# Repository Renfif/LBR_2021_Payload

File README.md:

# LBR 2021 Payload
PJS and UAS code for LBR USLI 2021
##

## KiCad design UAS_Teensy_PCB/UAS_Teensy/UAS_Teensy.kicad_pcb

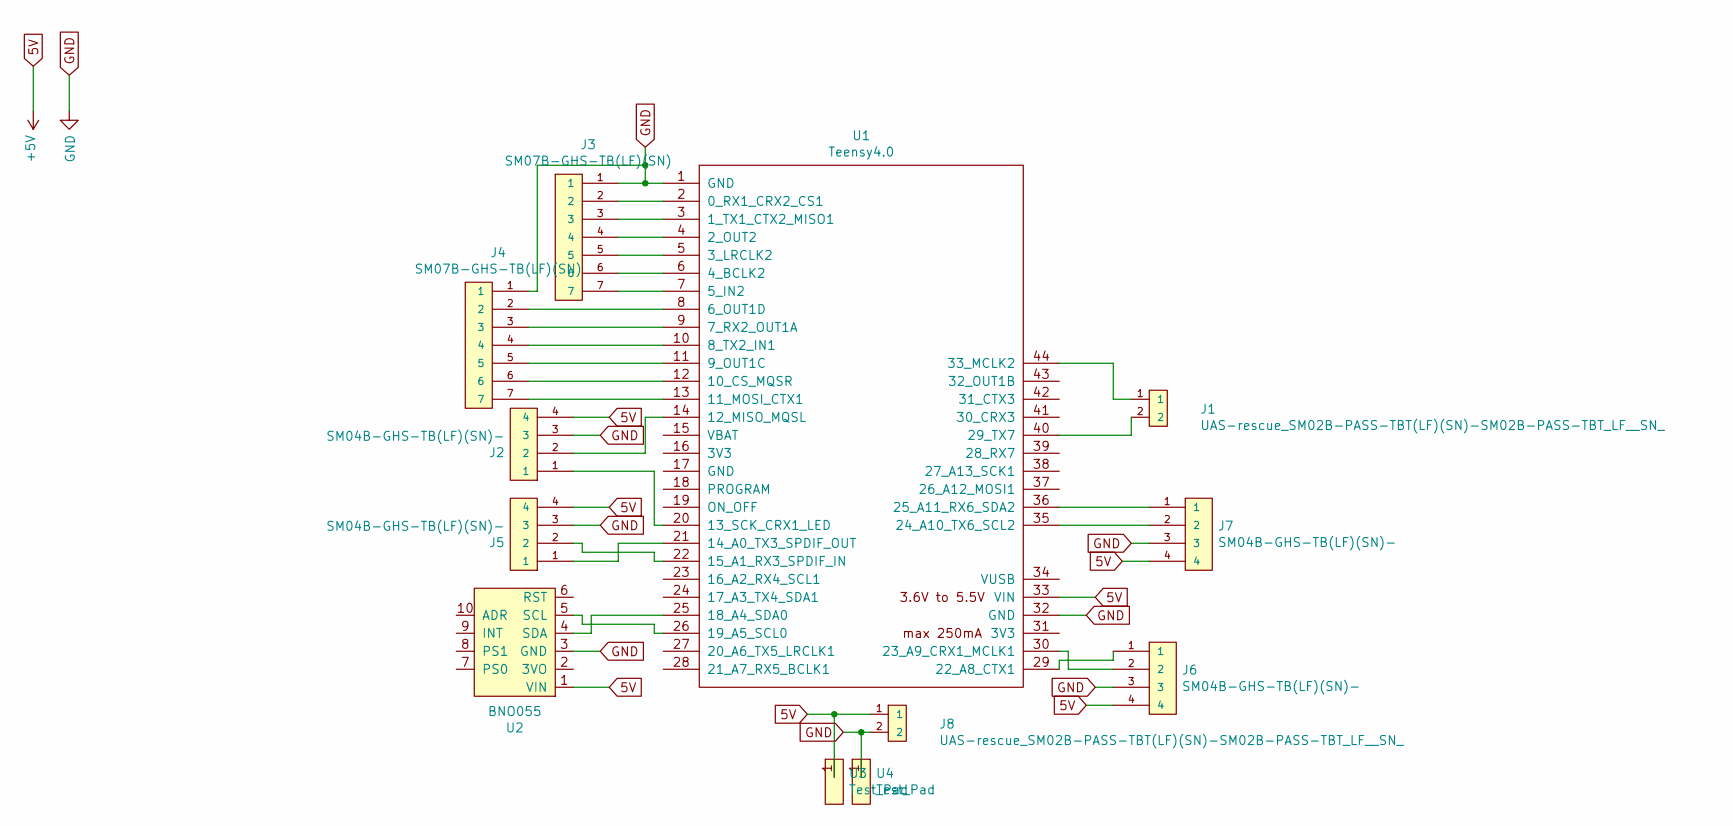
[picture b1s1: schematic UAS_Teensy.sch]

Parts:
J1, J8: UAS-rescue_SM02B-PASS-TBT(LF)(SN)-SM02B-PASS-TBT_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; SM02BGHSTBLFSN; PARTREV N/A
J2, J5, J6, J7: SM04B-GHS-TB(LF)(SN)-; JST_SM04B-GHS-TB(LF)(SN)-; PARTREV NA
J3, J4: SM07B-GHS-TB(LF)(SN); JST_SM08B-GHS-TB(LF)(SN); PARTREV NA
U1: Teensy4.0; Teensy40
U2: BNO055; BNO055_Breakout
U3, U4: Test_Pad; Individual_Solder_Pad

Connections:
5V: J2.4, J5.4, J6.4, J7.4, J8.1, U1.33 (VIN), U2.1 (VIN), U3.1
GND: J2.3, J3.1, J4.1, J5.3, J6.3, J7.3, J8.2, U1.1 (GND), U1.32 (GND), U2.3 (GND), U4.1
unnamed: J1.1, U1.44 (33_MCLK2)
unnamed: J1.2, U1.40 (29_TX7)
unnamed: J2.1, U1.20 (13_SCK_CRX1_LED)
unnamed: J2.2, U1.14 (12_MISO_MQSL)
unnamed: J3.2, U1.2 (0_RX1_CRX2_CS1)
unnamed: J3.3, U1.3 (1_TX1_CTX2_MISO1)
unnamed: J3.4, U1.4 (2_OUT2)
unnamed: J3.5, U1.5 (3_LRCLK2)
unnamed: J3.6, U1.6 (4_BCLK2)
unnamed: J3.7, U1.7 (5_IN2)
unnamed: J4.2, U1.8 (6_OUT1D)
unnamed: J4.3, U1.9 (7_RX2_OUT1A)
unnamed: J4.4, U1.10 (8_TX2_IN1)
unnamed: J4.5, U1.11 (9_OUT1C)
unnamed: J4.6, U1.12 (10_CS_MQSR)
unnamed: J4.7, U1.13 (11_MOSI_CTX1)
unnamed: J5.1, U1.21 (14_A0_TX3_SPDIF_OUT)
unnamed: J5.2, U1.22 (15_A1_RX3_SPDIF_IN)
unnamed: J6.1, U1.29 (22_A8_CTX1)
unnamed: J6.2, U1.30 (23_A9_CRX1_MCLK1)
unnamed: J7.1, U1.36 (25_A11_RX6_SDA2)
unnamed: J7.2, U1.35 (24_A10_TX6_SCL2)
unnamed: U1.25 (18_A4_SDA0), U2.4 (SDA)
unnamed: U1.26 (19_A5_SCL0), U2.5 (SCL)

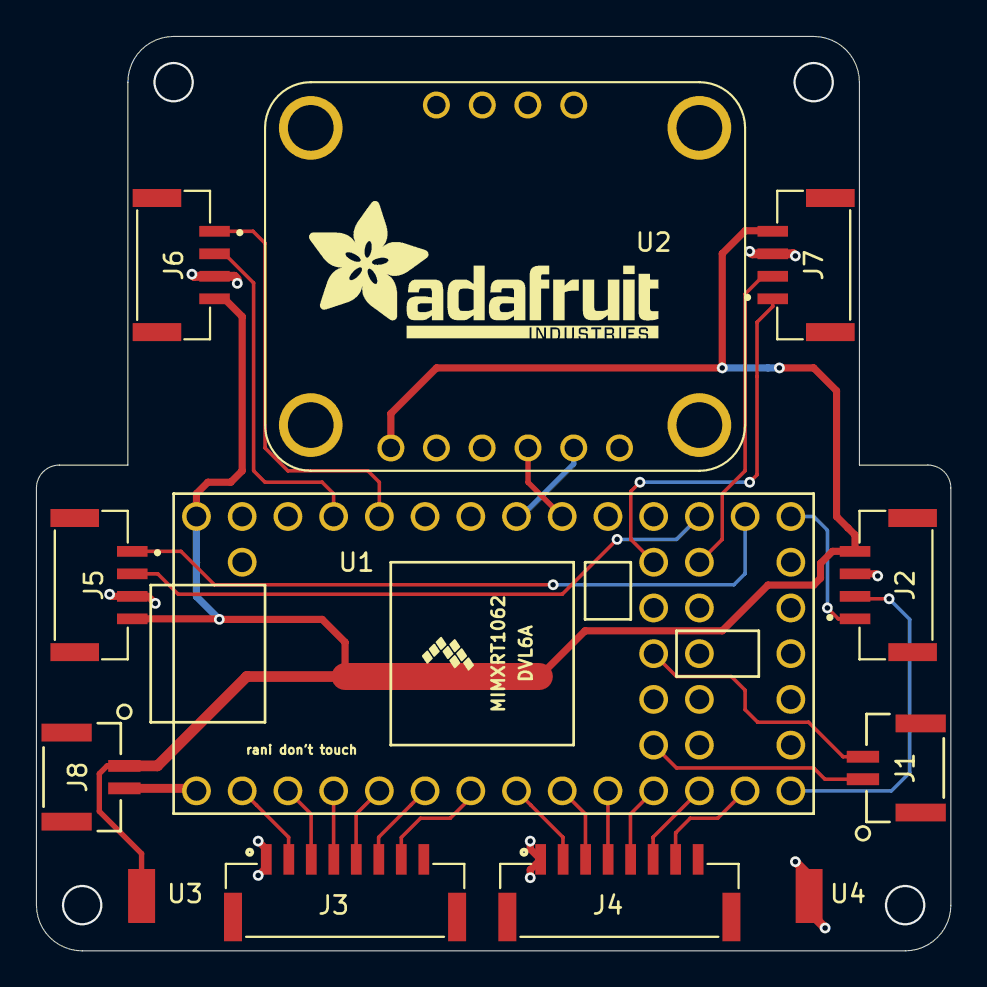
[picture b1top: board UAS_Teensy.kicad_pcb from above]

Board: 2 copper layers, 50.8 x 50.8 mm, 13 parts (0 on the bottom side), 26 nets.

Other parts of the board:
N2: V20180719; Label_version

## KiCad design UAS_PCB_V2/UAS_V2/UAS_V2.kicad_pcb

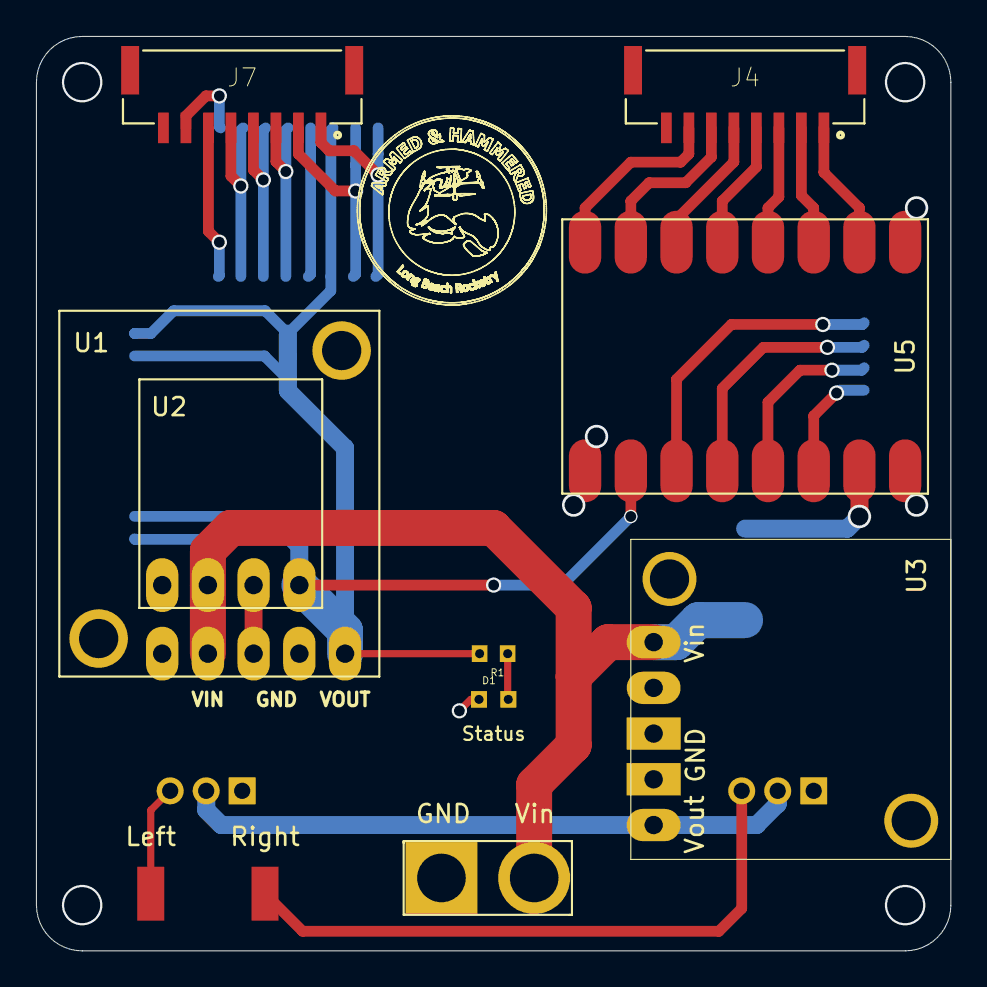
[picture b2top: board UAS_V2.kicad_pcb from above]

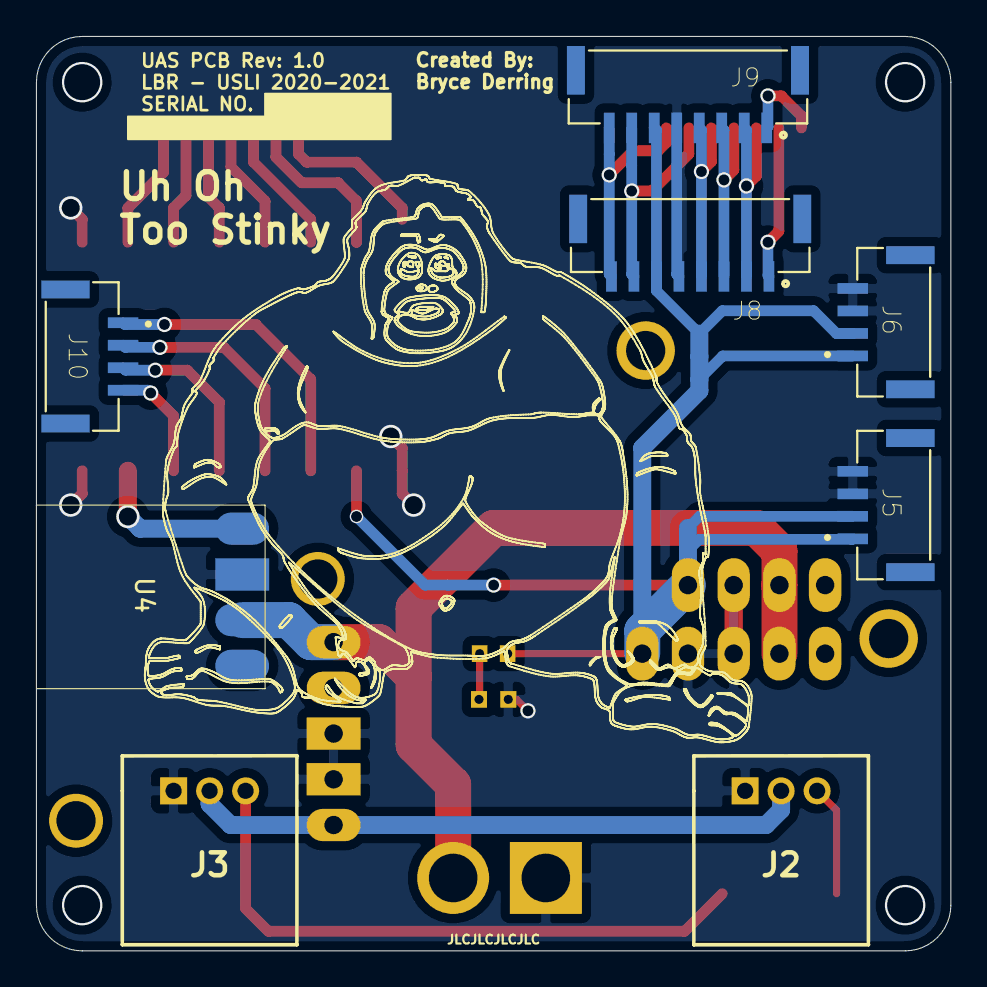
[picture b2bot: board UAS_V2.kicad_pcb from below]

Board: 2 copper layers, 50.8 x 50.8 mm, 20 parts (8 on the bottom side), 26 nets.

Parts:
D1: Device_LED; Indicator-LED
J1: UAS_PWR_IN; UAS_PCB_PWR_IN_PTOS
J2, J3: UAS_JST-3-pin-Revised-Symbol; MOLEX_SHDRRA3W50P0X200_1X3_0353630360
J4, J7: UAS_SM07B-GHS-TB(LF)(SN); JST_SM08B-GHS-TB(LF)(SN)
J5, J6, J10: UAS_SM04B-GHS-TB(LF)(SN)-; JST_SM04B-GHS-TB(LF)(SN)-
J8, J9: UAS_SM08B-GHS-TB(LF)(SN); JST_SM08B-GHS-TB(LF)(SN)
Left: UAS-rescue_Signal-Pad-UAS-cache; Individual_Solder_Pad
N2: V20180719; Label_version
R1: CR0603-JW-152ELF; RESC1608X55N
Right: UAS-rescue_Signal-Pad-UAS-cache; Individual_Solder_Pad
U1: UAS-rescue_5A-5V-Converter-UAS-cache; Pololu_5V_5A_Step_Down_Regulator
U2: UAS-rescue_500mA-5V-Converter-UAS-cache; Pololu_5V_500mA_Step_Down_Regulator
U3: 7.5V-2.5A-Step-Down(old); Pololu_7.75V_2.5A_Step_Down_Regulator(old)
U4: 12V_500mA_Step_Up; Pololu_12V_Step_Down_Regulator
U5: UAS-rescue_TB6612FNG-Dual-Motor-Driver-UAS-cache; Pololu_TB6612_Dual_Motor_Driver_Carrier_SMT

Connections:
+5V: J5.1, J5.2, J6.1, J6.2, J8.6, J9.6, R1.2, U1.5, U2.4, U5.2
+7.5V: J2.2, J3.2, U3.5
+12V: U4.4, U5.7
+24V: J1.2, U1.2, U2.2, U3.1, U4.2
GND: D1.1, J1.1, J2.1, J3.1, J5.3, J5.4, J6.3, J6.4, J8.5, J9.5, U1.3, U1.4, U2.3, U3.3, U3.4, U4.3, U5.1, U5.8, U5.16
unnamed: D1.2, R1.1
unnamed: J2.3, Left.1
unnamed: J3.3, Right.1
unnamed: J4.1, U5.15
unnamed: J4.2, U5.14
unnamed: J4.3, U5.13
unnamed: J4.4, U5.12
unnamed: J4.5, U5.11
unnamed: J4.6, U5.10
unnamed: J4.7, U5.9
unnamed: J7.1, J8.8, J9.8
unnamed: J7.2, J8.7, J9.7
unnamed: J7.3, J8.4, J9.4
unnamed: J7.4, J8.3, J9.3
unnamed: J7.5, J8.2, J9.2
unnamed: J7.6, J8.1
unnamed: J7.7, J9.1
unnamed: J10.1, U5.3
unnamed: J10.2, U5.4
unnamed: J10.3, U5.5
unnamed: J10.4, U5.6

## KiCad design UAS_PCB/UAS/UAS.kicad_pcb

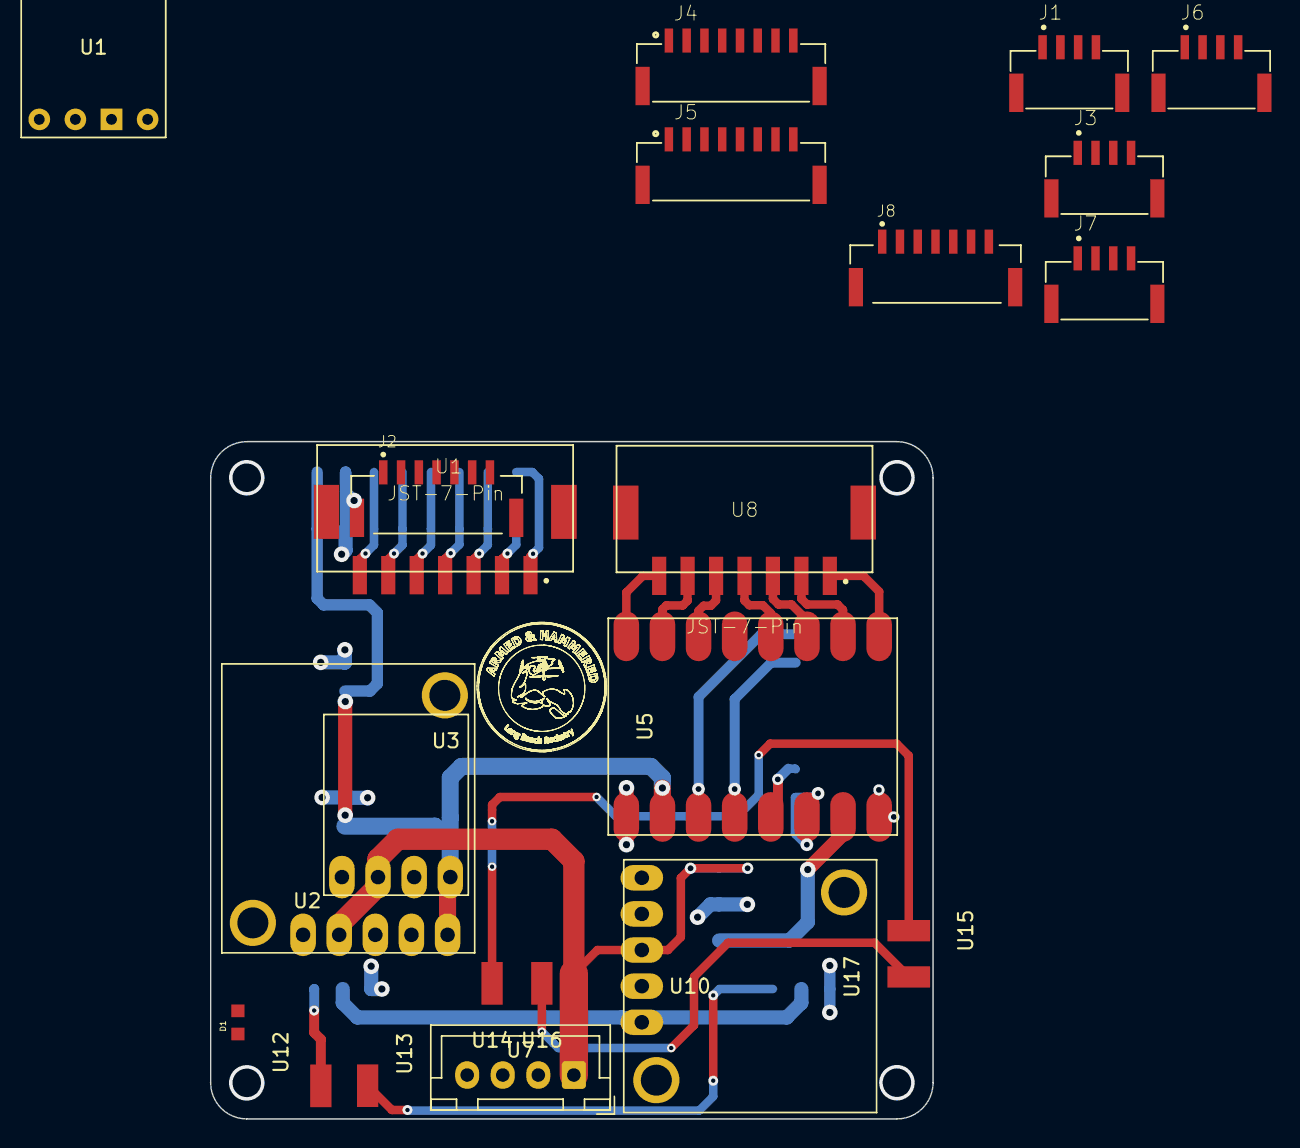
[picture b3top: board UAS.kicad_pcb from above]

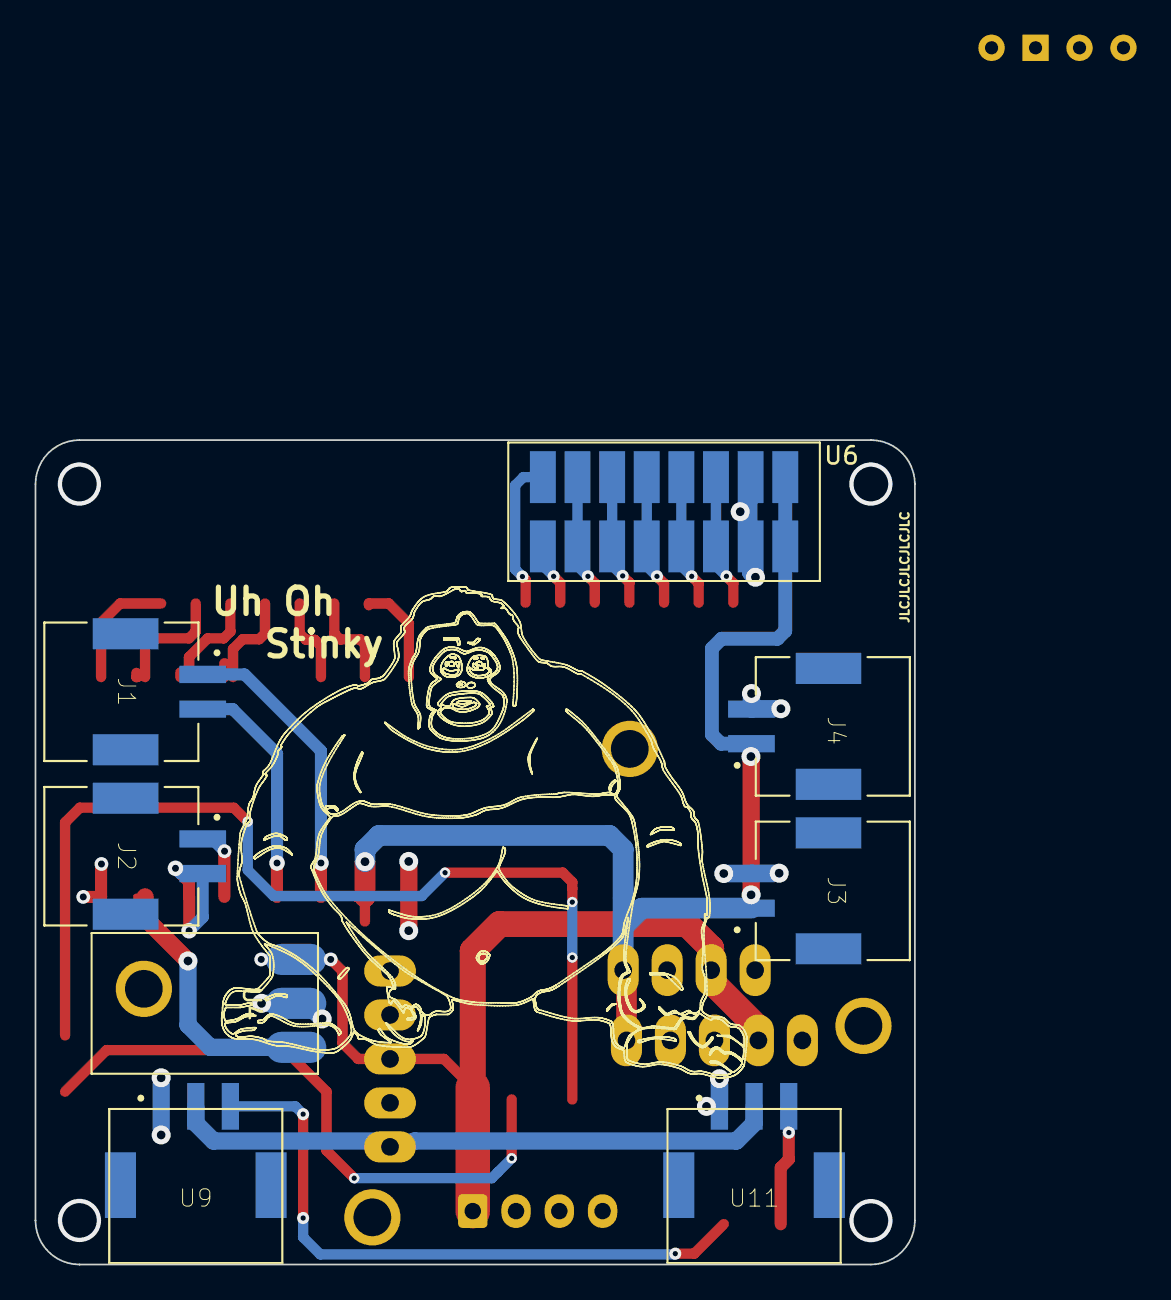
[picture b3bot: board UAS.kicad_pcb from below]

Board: 2 copper layers, 50.8 x 47.6 mm, 31 parts (8 on the bottom side), 36 nets.

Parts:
D1: LED; Indicator-LED
J1, J3, J6, J7: SM04B-GHS-TB(LF)(SN)-; JST_SM04B-GHS-TB(LF)(SN)-
J1#2, J2#2, J3#2, J4#2: SM02B-PASS-TBT; JST_SM02B-PASS-TBT(LF)(SN)
J2, J8: SM07B-GHS-TB(LF)(SN); JST_SM07B-GHS-TB(LF)(SN)
J4, J5: SM08B-GHS-TB(LF)(SN); JST_SM08B-GHS-TB(LF)(SN)
U1: 12V-500mA-StepDown
U1#2, U8: JST-7-Pin; JST_SM07B-PASS-TBT(LF)(SN)
U2: 5A-5V-Converter; Pololu_5V_5A_Step_Down_Regulator
U3: 500mA-5V-Converter; Pololu_5V_500mA_Step_Down_Regulator
U4: 12V-StepUp-Converter; Pololu_12V_Step_Up_Voltage_Regulator_SMT
U5: TB6612FNG-Dual-Motor-Driver; Pololu_TB6612_Dual_Motor_Driver_Carrier_SMT
U6: 16_Pad_2x8_Set-UAS-cache; 16_Pad_Set_2mm_pitch
U7: UAS-rescue_JST-4-Pin-UAS-cache; JST_XH_B4B-XH-A_1x04_P2.50mm_Vertical
U9, U11: JST-3-Pin; JST_SM03B-PASS-TBT(LF)(SN)
U10: UAS-rescue_7.5V-2.4A-Converter-UAS-cache; Pololu_7.75V_2.4A_Step_Down_Regulator
U12, U13: Signal-Pad; Individual_Solder_Pad
U14, U15, U16, U17: UAS-rescue_Signal-Pad-UAS-cache; Individual_Solder_Pad

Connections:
+5V: J3#2.1, J4.8, J4#2.1, J5.8, J6.1, J6.2, J7.1, J7.2, U3.4, U6.15, U6.16
+7.5V: U9.2, U10.5, U11.2
+12V: U1.2, U2.2, U4.1, U7.1, U10.3
GND: J3#2.2, J4#2.2, U1.3, U4.2, U6.13, U6.14, U7.4, U9.1, U10.4, U11.1
unnamed: J1.1, J1.2, J1#2.1, U5.3
unnamed: J1.3, J1.4, U5.4
unnamed: J2.1, J2#2.1, J4.1
unnamed: J2.2, J2#2.2, J5.1
unnamed: J2.3, J4.2, J5.2
unnamed: J2.4, J4.3, J5.3
unnamed: J2.5, J4.4, J5.4
unnamed: J2.6, J4.5, J5.5
unnamed: J2.7, J4.6, J5.6
unnamed: J3.1, J3.2, U5.6
unnamed: J3.3, J3.4, U5.5
unnamed: J4.7, J5.7, J6.3, J6.4, J7.3, J7.4, U3.3
unnamed: J8.1, U5.16
unnamed: J8.2, U5.15
unnamed: J8.3, U5.14
unnamed: J8.4, U5.13
unnamed: J8.5, U5.11
unnamed: J8.6, U5.10
unnamed: J8.7, U5.9
unnamed: U1.1, U1#2.1, U6.1
unnamed: U1#2.2, U6.2
unnamed: U1#2.3, U6.3, U6.4
unnamed: U1.4, U1#2.4, U5.7, U6.5, U6.6
unnamed: U1#2.5, U6.7, U6.8
unnamed: U1#2.6, U6.9, U6.10
unnamed: U1#2.7, U6.11, U6.12
unnamed: U2.3, U2.4, U5.1, U5.8
unnamed: U2.5, U5.2
unnamed: U11.3, U12.1
unnamed: U9.3, U13.1
unnamed: U14.1, U15.1
unnamed: U16.1, U17.1

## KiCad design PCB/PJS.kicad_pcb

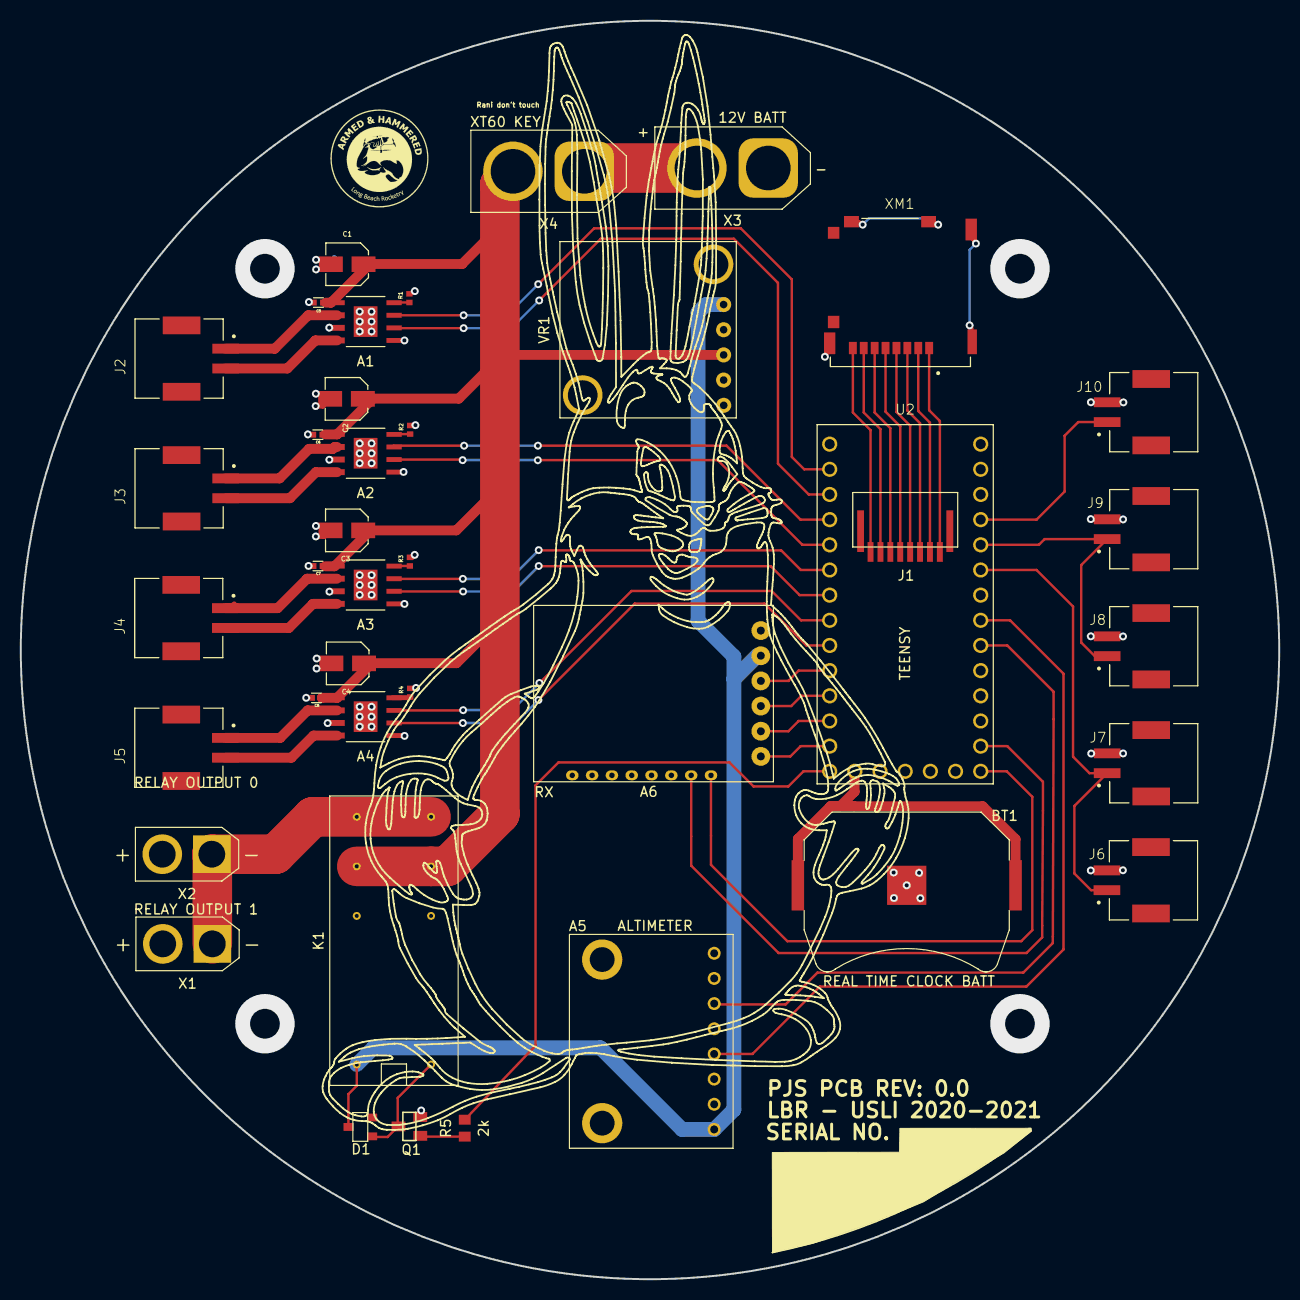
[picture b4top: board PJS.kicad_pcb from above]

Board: 2 copper layers, 127.0 x 127.0 mm, 40 parts (0 on the bottom side), 48 nets.

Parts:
A1, A2, A3, A4: DRV8871_MotorDriver
A5: BMP388_Altimeter
A6: TBS_Crossfire_RF_Receiver
BT1: 36-3034-ND_CoinCellHolder
C1, C2, C3, C4: 47uF; EEE-1CA470SP_Capacitor
C5, C6, C7, C8: 0.1uF; CL05B104KO5NNNC_Capacitor
D1: D_Schottky; 1SS351-TB-E_Diode
J1: HFW8R-1STE1H1LF_FFC
J2, J3, J4, J5: SM02B-PASS-TBT_Connector
J6, J7, J8, J9, J10: SM02B-PASS-TBT_SwitchConnector; SM02B-PASS-TBT_Connector
K1: G2R-2-DC5_Relay
Q1: MMBT222A_Transistor; MMBT2222A_Transistor
R1, R2: 30k; 0402_Resistor
R3, R4: 82k; 0402_Resistor
R5: 2k; ERA-6AEB202V
U2: Teensy4.0
VR1: D24V22F5_VoltageRegulator
X1, X2: XT30-F_MotorConnector; AMASS_XT30U-F_1x02_P5.0mm_Vertical
X3, X4: XT60-F_BatteryConnector; AMASS_XT60-M_1x02_P7.20mm_Vertical
XM1: MicroSD_Slot

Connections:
+5V: A5.1, A6.2, D1.3, K1.1, VR1.5
+12V: A1.5, A2.5, A3.5, A4.5, C1.1, C2.1, C3.1, C4.1, C5.1, C6.1, C7.1, C8.1, K1.3, K1.6, VR1.3, X4.2
/3.3V_Coin: BT1.1, U2.VBAT
/Alt_SCK: A5.4, U2.19
/Alt_SDI: A5.6, U2.18
/Door_RelayOut1: K1.5, X1.1, X2.1
/Link_DriverIN1: A2.3, U2.2
/Link_DriverIN2: A2.2, U2.3
/Link_DriverOUT1: A2.6, J3.1
/Link_DriverOUT2: A2.8, J3.2
/LockA_DriverIN1: A3.3, U2.4
/LockA_DriverIN2: A3.2, U2.5
/LockA_DriverOUT1: A3.6, J4.1
/LockA_DriverOUT2: A3.8, J4.2
/LockB_DriverIN1: A4.3, U2.6
/LockB_DriverIN2: A4.2, U2.7
/LockB_DriverOUT1: A4.6, J5.1
/LockB_DriverOUT2: A4.8, J5.2
/RF_CH1: A6.3, U2.8
/RF_CH2: A6.4, U2.9
/RF_CH3: A6.5, U2.10
/RF_CH4: A6.6, U2.11
/RF_CH5: A6.7, U2.13
/RF_CH6: A6.8, U2.14
/Relay_Signal: R5.2, U2.12
/S1_Link: J6.1, J7.1, U2.21
/S2_Door: J8.1, J9.1, U2.22
/S3_UAS: J10.1, U2.23
/UAS_DriverIN1: A1.3, U2.0
/UAS_DriverIN2: A1.2, U2.1
/UAS_DriverOUT1: A1.6, J2.1
/UAS_DriverOUT2: A1.8, J2.2
GND: A1.1, A1.7, A2.1, A2.7, A3.1, A3.7, A4.1, A4.7, A5.3, A6.1, BT1.2, C1.2, C2.2, C3.2, C4.2, C5.2, C6.2, C7.2, C8.2, J6.2, J7.2, J8.2, J9.2, J10.2, Q1.2, R1.2, R2.2, R3.2, R4.2, U2.G1, VR1.4, X1.2, X2.2, XM1.9
unnamed: A1.4, R1.1
unnamed: A2.4, R2.1
unnamed: A3.4, R3.1
unnamed: A4.4, R4.1
unnamed: D1.1, K1.8, Q1.3
unnamed: J1.1, XM1.1
unnamed: J1.2, XM1.2
unnamed: J1.3, XM1.3
unnamed: J1.4, XM1.4
unnamed: J1.5, XM1.5
unnamed: J1.6, XM1.6
unnamed: J1.7, XM1.7
unnamed: J1.8, XM1.8
unnamed: Q1.1, R5.1
unnamed: X3.2, X4.1

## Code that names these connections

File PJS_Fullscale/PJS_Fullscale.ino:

//Switch pins
#define Switch1_Link
#define Switch2_Door
#define Switch3_UAS

//Driver pins
#define UAS_DriverIN1 0 
#define UAS_DriverIN2 1
#define Link_DriverIN1 2
#define Link_DriverIN2 3
#define LockA_DriverIN1 4
#define LockA_DriverIN2 5
#define LockB_DriverIN1 6
#define LockB_DriverIN2 7
#define Relay_Signal 12

//Receiver pins
#define RF_CH1 8
#define RF_CH2 9
#define RF_CH3 10
#define RF_CH4 11
#define RF_CH5 13
#define RF_CH6 14

//Altimeter pins - Ifeoma add whatever you need 
#define Alt_SDI 18
#define Alt_SCK 19

//SD Card pins 
#define SD_DAT0 35 
#define SD_DAT1 34
#define SD_DAT2 39
#define SD_DAT3 38
#define SD_CMD 37 
#define SD_CLK 36



//getting signal to perform operations manually OR another condition is met 


//all switches are clicked closed 
//1 switch is normally closed and when UAS releases it is LOW
//2 switches check if doors are closed, and are HIGH when closed  
//2 switches for the linkage arm normally open, HIGH when door is oopen

//ch1 is an arming switch 



void loop() {

  //get stuff from receiver. Only getting CH2 - CH6 input during installation and setup
  Ch1 = receive(Receiver1) //Arming Switch
  Ch2 = receive(Receiver2)
  Ch3 = receive(Receiver3) 
  Ch4 = receive(Receiver4)
  Ch5 = receive(Receiver5) 
  Ch6 = receive(Receiver6)

  //if arming switch is on, execute the following
  if(Ch1 > 200) { 
    main(Ch2, Ch3, Ch4)
  }
   
}

int Receive(ReceiverX) { 
  
  int Ch=pulseIn(ReceiverX,HIGH,25000);
  
  Ch=pulseToPWM(Ch);

  return Ch;

}


int pulseToPWM(int pulse){
  if (pulse>1000){
    pulse = map(pulse, 1000, 2000, -500, 500);
    pulse = constrain(pulse, -255,255);  
  }else{
    pulse=0;  
  }
  if(abs(pulse)<= deadzone){
    pulse=0;
  }
  return pulse;
}


void main() { 

  //Time = _______________________ (real time clock function)

  //if channel says, unlock door, also consider considering for relay

  if(Switch2_Door == HIGH) and (altimeter is correct)) or (Ch2 > 0) { 
    UnlockDoor(Ch2, Time) // is start of procedure dictated by human control or altimeter? 
   
    if((Switch2_Door == HIGH) and (altimeter is correct)) or (Ch3 > 0) {
       delay(5000);
       OpenDoor(Time)
       
       }

  }

   
  //if door open, and altimeter is clear, deploy UAS
  
  if((Switch1_Link == HIGH) and (altimeter is correct)) or (Ch4 > 0) { 
    UAS_Deploy(Time)
    } 


  //if UAS is deployed, limit switch and/or timing, close door, also consider considering for relay

  if(Switch3_UAS == LOW) and (altimeter is correct)) or (CH5 > 0) { 
    
    CloseDoor(Time) 
    
    } 


}


void UnlockDoor(Time) { 

  //unlock door 
  //write to datalogging program
 
}


void OpenDoor(Time) { 
  //open door 
  //write to datalogging program

  
  
}

void UAS_Deploy(Time) { 
  //deployUAS
  //write to datalogging program
  analogWrite(UAS_DriverIN1, 255); 
  analogWrite(UAS_DriverIN2, 0);
  
}

void CloseDoor(Time) { 
  //deployUAS 
  //write to datalogging program

}

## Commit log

2020-12-21 Component test/example files and PJS Firmware rev1 with no data collection implemented
2020-12-29 changed file name
2020-12-31 Schematic and footprints of PJS.
    Does not include the Pololu driver in the schematic, though the pins are defined on the Teensy.
    The footprints for the DRV8871 Aux Motor Driver and the transistor, as well as associated components, are not updated.
2020-12-31 Current Schematic and Footprints.
    Pins between schematic and footprint are now mostly in alignment. The altimeter has a footprint, and JST connectors are to size.
2021-01-01 99% Complete Schematic and Footprints.
    The only items on the schematic that are not complete are the switches, as the 5th switch needs to be defined and all of them should be renamed.
    Some of the Teensy pins are not named properly either. Besides that, every component should be correctly associated with an accurate footprint.
2021-01-01 library localization fixes
    confuses library paths and missing files solved by including them within the realm of the github folder instead of local documents
2021-01-01 teensy breakout, limit switch connection, dxf for board
    added teensy breakout to schematic, and added missing limit switch connections. also inserted DXF of board dimensions to the PCB file (le monke)
2021-01-02 Jumper Connector
2021-01-02 99.5% Complete Schematic and Footprint
    The only item missing is the footprint for the RF receiver, which is now being mounted on the board.
    Connectors for the motors and switches have now changed to two different locking JSTS.
2021-01-02 changed table location for library
2021-01-02 Replacement files
2021-01-02 more table changes
2021-01-02 Completed schematic and PCB layout
    No components have .step files for rendering. The only footprint that is incorrect is the RF receiver, which is not yet mounted ion the board.
2021-01-02 Adding first round of 3D Models to Footprints
2021-01-02 PCB with updated Altimeter footprint
2021-01-02 Updated DRV8871 footprint
2021-01-02 more 3d models
2021-01-02 cap 3d models
2021-01-02 Schematic and PCB
    First version with traces.
2021-01-02 3d file revisions
2021-01-02 RX footprint
2021-01-02 PCB with TBS RF Receiver
    All traces are connected. Planes and layers are not defined
2021-01-02 almost all 3d models
    a few minor bugs fixed, but traces should be redone after CDR and the bugs are mostly to do with weird footprint things
2021-01-02 Receiver fix and drv resistor fix
2021-01-02 receiver update
2021-01-02 Updated connector symbols
2021-01-03 Nearly Finished PCB
    Requires resizing footprint for the altimeter. New resistors on the motor driver ICs need to be implemented. Perhaps ground planes/heat dissapation should be added to the driver ICs.
2021-01-03 Teensy 3D Details
2021-01-03 Model Adjustments
2021-01-03 Silkscreen Memes and Clear Relay CAD
2021-01-03 More Silkscreens and 3d Memes
    Payload Logo and pin color fixes
2021-01-03 latest version with models and silkscreens
2021-01-03 rendering
2021-01-03 Relay 3D Fix
2021-01-03 xt30 fixed
2021-01-03 silkscreen adjustments
2021-01-09 Grounded DRV8871s, sizde traces, and general neatness
    There are now vias to for the motor drivers to manage heat. Capacitors were moved slightly. Traces are now sized, and aligned.
    There is huge overhead for each trace, with the exception of signal.
    The two issues that still need to be addressed are the XT60s and the Relay, both of which are not going to the right pins.
2021-01-11 Finished PCB
    All traces are sized and spaced. The XT60 and relay pins are fixed.
2021-01-11 first gerber files created
    not sure if these ones are retarded but i followed JLC's instructions
2021-01-23 1.22.21 18_29PM PJS Fullscale
    Defined pins, setup functions for receiving manual control. Lots of Pseudocode used to setting up the logic.
2021-02-04 File Organization and UAS test code added
    lds testing for UAS has begun
2021-02-13 PJS Fullscale Draft
2021-02-13 PJS Fullscale Draft
    Changed the locking door function to be on only for the total duration that is set.
2021-02-14 pcb test code
2021-02-14 Test code still doesnt work for some odd reason
2021-02-14 PJS Test Code Fixed and LDS PID prototype
2021-02-15 Visual Teensy Environment For LDS
2021-02-20 Added SD Card Datalogging
2021-02-23 UAS PCB Start
2021-02-23 cutout profile
2021-02-23 Footprints
2021-02-23 schematic drawing
2021-02-23 uh oh
2021-02-23 graphics
2021-02-24 symbol update - rani
    lol
2021-02-24 for realsies we got it sent baybee - rani
    symbol
2021-02-24 filename change
2021-02-24 Symbols oriented on schematic
2021-02-25 schematic connections update
    we need to fix these god awful connector symbols, sorry rani lol
2021-02-25 Pad Symbol
2021-02-25 JST Connector Footprints and Models
2021-02-25 First Layout Attempt and Updated Footprints
    needs a rework and a dimension change/shape change
2021-02-25 attempting to pack things on back side cause im told we have the clearance to do so, still a possibility we need larger board or more than 2 layers
    also considering ditching passthrough for PCS cameras.
2021-02-26 added 3d Models
2021-02-26 graphics fix
2021-02-26 added PWM signal testpad
2021-02-26 footpirnt placement changes, need room for traces
2021-02-26 fixed courtyard errors
2021-02-26 SMT TB6612
2021-02-26 First traces
2021-02-26 Routing Traces
    All traces besides the top connectors are routed, but the top connector pads need to be rearranged. The ground plane still need to be placed. Trace widths still need to be set.
2021-02-27 Datalogging Solo File Addition
    still has bugs, awaiting full version
2021-02-27 fixed datalogging only
2021-02-27 doesnt work for some reason, idk whats wrong
    cannot find sd card, continues to print errorcheck "Card failed, or not present". either an electrical/sd card issue or something to do with sdfat library not working nicely with sdioconfig or vice v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
2021-02-27 slight rearranging and pin changes, PCS connector on top still needs to be reorganized for a straight shot
    also, for gods sake we gotta change the symbols for connectors on the diagram
2021-02-27 fixed connector, 12v trace needs to be bigger for sure , probably close to 1.5mm
    symbols are still messy FeelsBadMan
2021-02-27 fixed 3d view
2021-02-27 label fix
2021-02-27 slight adjustments to footprint placement
2021-02-27 added LeMonke Graphics, still needs trace width adjustments
2021-02-27 3d Model
2021-02-28 trace width changes
2021-02-28 flipped PCS connector to front
2021-02-28 Update UAS.kicad_pcb-bak
2021-02-28 12v step up was backwards
    should double check other pinouts as well
2021-02-28 swapping front logo
2021-02-28 Some vias and traces repositioned
2021-02-28 Pair of traces moved
2021-03-01 trace width changes
    i blame rani, still need lbr payload logo
2021-03-01 final version with kyles passthrough pads and graphics
2021-03-01 uas pcb files updated to latest version in ranis hellscape
2021-03-01 filled ground plane attempt 1
2021-03-01 fill numba 2
2021-03-01 renders
2021-03-01 gerber files
2021-03-01 more gerbers
2021-03-01 silkscreen fix and new gerbers
2021-03-01 change to different 3 pin connectors
    the original ones were out of stock and the new ones are through hole and slightly longer, this required some shifting of parts. new version clears DRC and looks fine
2021-03-01 gerbers for new design
2021-03-01 silkscreen fix
2021-03-01 final trace width fix
2021-03-01 gerber for final trace fix
2021-03-01 oh boy another new 3 pin connector
2021-03-01 swapped in the molex connectors and generated gerbers for this board
2021-03-01 zipped file and renders
2021-03-13 PJS 90% Finished Program
    Logic should be good. SD and RTC libraries are not implemented. Datalogging header file draft is included, but not imported.
2021-03-13 autoleveling test 1
2021-03-13 LDS PID changes
2021-03-20 Finished PJS Program
2021-03-24 Final PJS Program
2021-03-25 Fullscale Final Program
    removed switch requirements on individual manual
2021-03-25 manual mode switch fixes
2021-03-26 UAS Install speed change
2021-03-26 changing directions for motors and some logic
2021-03-26 more logic changes, deployment sequence doesnt work properly still, UAS stuff doesnt go. also the altimeter based control remains untested.
2021-04-07 UAS Schematic/Footprint Updates
    Nothing for the board layout has been worked on yet, schematic is done except for stuff like diodes or whatever I haven't confirmed w/ u guys
2021-04-08 Updates To UAS PCB
    update #based
2021-04-08 Removing Diodes
    Just removing the diodes from schematic
2021-04-10 JST 3-Pin cleanup
    I cleaned it (?)
2021-04-10 12V Converter Added
    read title
2021-04-10 Indicator LED and Wiring
    I push too often but #grindGithubCommits
2021-04-12 templates
2021-04-12 bno footprint
2021-04-12 teensy symbol
2021-04-12 no more squantor
2021-04-12 symbol lib added for rani kiss kiss
2021-04-12 Teensy PCB Prep V1
    First prep to make all connections in Teensy PCB.
    List of Things To Add:
    - Footprint for two pin connector
    - On Layout side, DXF import of edges of PCB (Size 1.6x1.8in)
2021-04-12 teensy footprint update
2021-04-12 Teensy Board Prep V1.1
    Updated the Teensy Footprint/Symbol to match. Added entire Teensy library in case we just decided to use a Teensy 1.0 #businessMindset
2021-04-12 2 pin footprint
2021-04-12 pcb dxf updates
2021-04-13 Schematic Wiring V1
    First Step in Schematic Wiring
2021-04-14 Teensy PCB Ready To Wire Up Update
    Schematic is finalized and all that's left is to lay traces
2021-04-14 Teensy PCB Finished, Validation Next
    Teensy PCB is done, just need to validate the board design and order.
2021-04-16 trace changes and fill for teensy pcb
2021-04-16 Teensy Board Updates
    Teensy Board Updates
2021-04-16 power in duh
2021-04-16 For Realsies Final Teensy PCB
    lol
2021-04-16 final version
2021-04-17 UAS_PCB_V2 updated version
    almost ready to merge teensy and uas v2 to master
2021-04-17 footprint file system fixes
2021-04-17 finalized merge
2021-04-19 UAS PDP PCB Models
2021-04-19 teensy pcb models
2021-04-20 photo

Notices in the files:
parts and their libraries:
Copyright 2016 Accelerated Designs. All rights reserved.
